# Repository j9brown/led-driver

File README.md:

# LED Driver

Drives 4 RGB/W LEDs with PWM for a total of up to 3 A controlled over an I2C bus.

## Design

This design is based around a [PCA9685](https://www.nxp.com/docs/en/data-sheet/PCA9685.pdf) I2C PWM chip with 16 channels.  Each channel drives an N-channel MOSFET low-side switch.  Each group of 4 channels and a positive common rail feeds a JST XH 5-pin connector to which an RGB/W LED lamp may be attached.

The I2C bus must be referenced to the same ground as the negative input.

The board is designed for use with a 12 V nominal power supply but should work with anything from about 5 V to 16 V.  It includes a 3 A polyfuse and transient voltage suppression.  In case of reverse polarity connection, the TVS shunts the power input across the polyfuse.

## Notice

The software, documentation, design, and all copyright protected artifacts are released under the terms of the [MIT license](LICENSE).

The hardware is released under the terms of the [CERN-OHL-W license](hardware/LICENSE).

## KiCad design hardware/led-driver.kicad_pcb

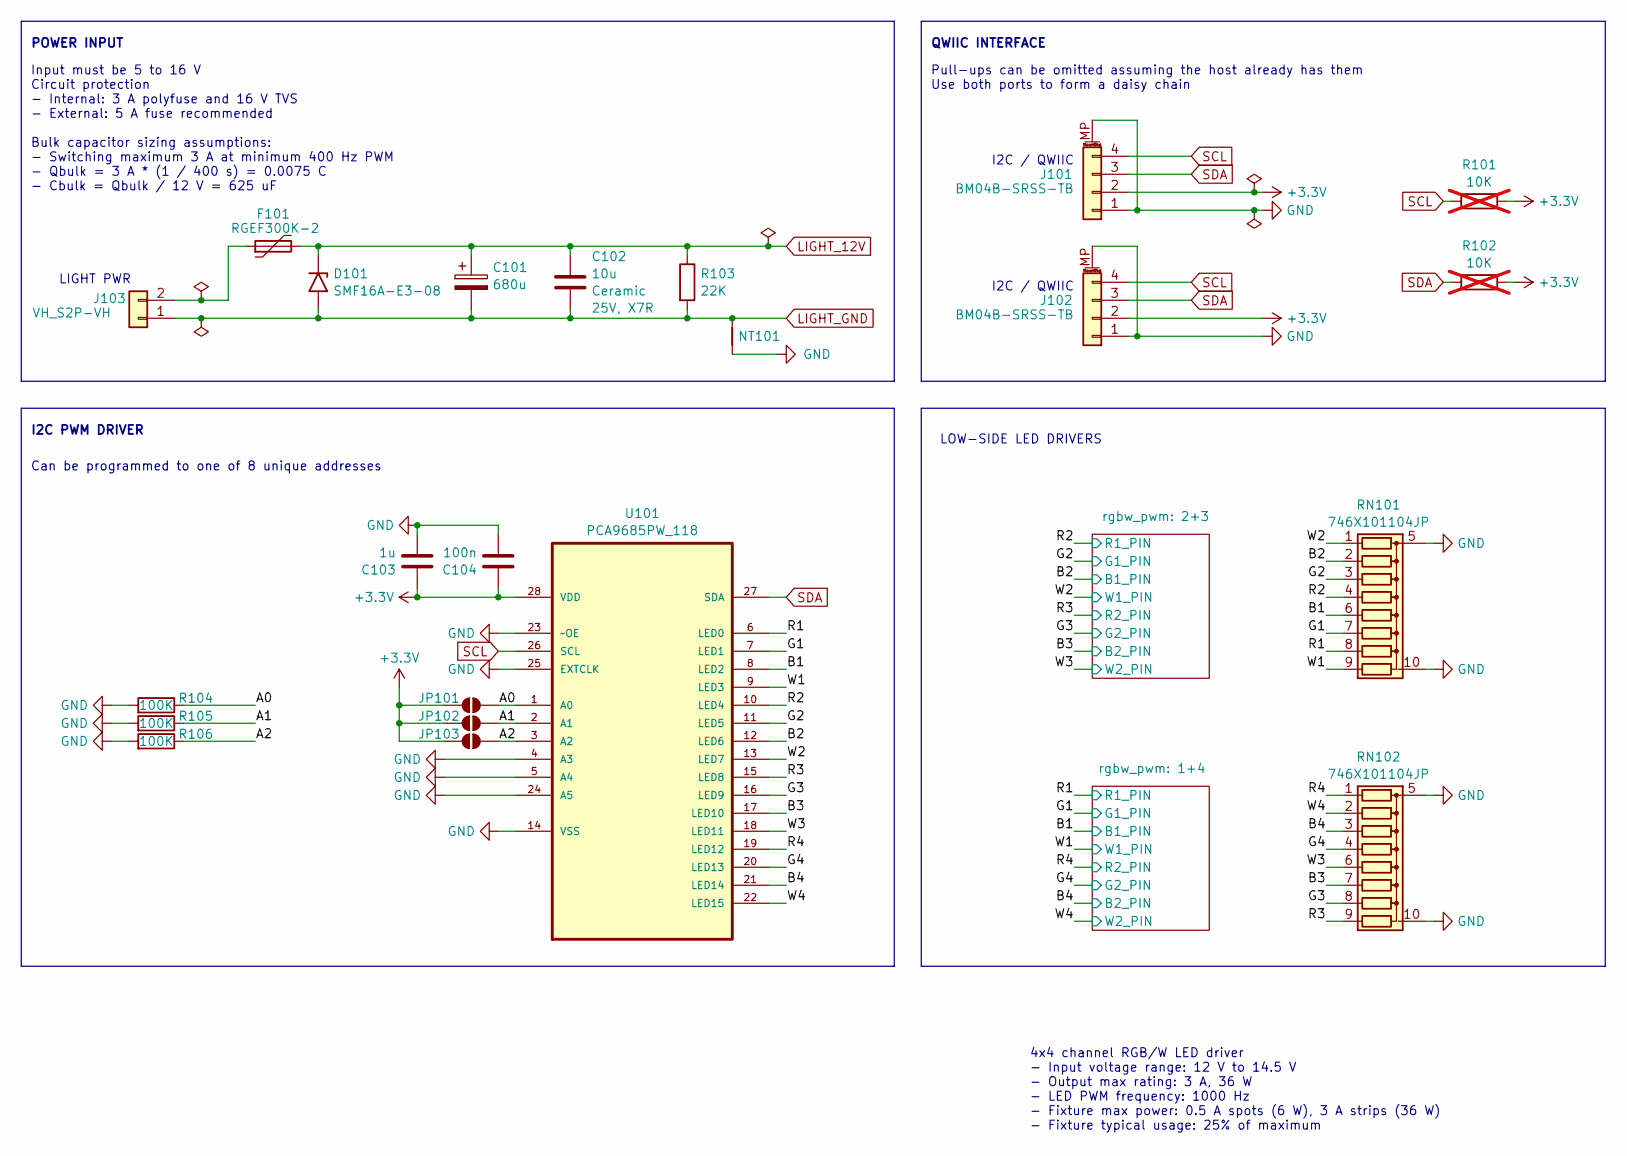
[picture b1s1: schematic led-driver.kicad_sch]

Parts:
C101: 680u; CP_Radial_D10.0mm_P5.00mm; Part EKZH160ELL681MJC5S
C102: 10u; C_1206_3216Metric_Pad1.33x1.80mm_HandSolder; Rating 25V, X7R
C103: 1u; C_0603_1608Metric_Pad1.08x0.95mm_HandSolder
C104: 100n; C_0603_1608Metric_Pad1.08x0.95mm_HandSolder
D101: SMF16A-E3-08; D_SMF
F101: RGEF300K-2; FUSRR505W81L660T250H1360
J101, J102: BM04B-SRSS-TB; JST_SH_BM04B-SRSS-TB_1x04-1MP_P1.00mm_Vertical
J103: VH_S2P-VH; JST_VH_S2P-VH_1x02_P3.96mm_Horizontal
JP101, JP102, JP103: SolderJumper_2_Open; SolderJumper-2_P1.3mm_Open_TrianglePad1.0x1.5mm
NT101: NetTie_2; NetTie-2_SMD_Pad1.6mm
R101, R102: 10K; R_0603_1608Metric_Pad0.98x0.95mm_HandSolder; not fitted
R103: 22K; R_1206_3216Metric_Pad1.30x1.75mm_HandSolder
R104, R105, R106: 100K; R_0603_1608Metric_Pad0.98x0.95mm_HandSolder
RN101, RN102: 746X101104JP; RESCAXS64P320X160X70-10N
U101: PCA9685PW_118; SOP65P640X110-28N; MPN PCA9685PW,118

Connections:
+3.3V: C103.1, C104.1, J101.2, J102.2, JP101.1 (A), JP102.1 (A), JP103.1 (A), R101.1, R102.1, U101.28 (VDD)
/A0: JP101.2 (B), R104.1, U101.1 (A0)
/A1: JP102.2 (B), R105.1, U101.2 (A1)
/A2: JP103.2 (B), R106.1, U101.3 (A2)
/B1: RN101.6 (R5), U101.8 (LED2); also elsewhere on the board
/B2: RN101.2 (R2), U101.12 (LED6); also elsewhere on the board
/B3: RN102.7 (R6), U101.17 (LED10); also elsewhere on the board
/B4: RN102.3 (R3), U101.21 (LED14); also elsewhere on the board
/G1: RN101.7 (R6), U101.7 (LED1); also elsewhere on the board
/G2: RN101.3 (R3), U101.11 (LED5); also elsewhere on the board
/G3: RN102.8 (R7), U101.16 (LED9); also elsewhere on the board
/G4: RN102.4 (R4), U101.20 (LED13); also elsewhere on the board
/R1: RN101.8 (R7), U101.6 (LED0); also elsewhere on the board
/R2: RN101.4 (R4), U101.10 (LED4); also elsewhere on the board
/R3: RN102.9 (R8), U101.15 (LED8); also elsewhere on the board
/R4: RN102.1 (R1), U101.19 (LED12); also elsewhere on the board
/W1: RN101.9 (R8), U101.9 (LED3); also elsewhere on the board
/W2: RN101.1 (R1), U101.13 (LED7); also elsewhere on the board
/W3: RN102.6 (R5), U101.18 (LED11); also elsewhere on the board
/W4: RN102.2 (R2), U101.22 (LED15); also elsewhere on the board
GND: C103.2, C104.2, J101.1, J101.MP (MountPin), J102.1, J102.MP (MountPin), NT101.1, R104.2, R105.2, R106.2, RN101.5 (common), RN101.10 (common), RN102.5 (common), RN102.10 (common), U101.4 (A3), U101.5 (A4), U101.14 (VSS), U101.23 (~OE), U101.24 (A5), U101.25 (EXTCLK)
LIGHT_12V: C101.1, C102.1, D101.1 (A1), F101.2, R103.1; also elsewhere on the board
LIGHT_GND: C101.2, C102.2, D101.2 (A2), J103.1, NT101.2, R103.2; also elsewhere on the board
unnamed: F101.1, J103.2
SCL: J101.4, J102.4, R101.2, U101.26 (SCL)
SDA: J101.3, J102.3, R102.2, U101.27 (SDA)

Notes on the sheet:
4x4 channel RGB/W LED driver - Input voltage range: 12 V to 14.5 V - Output max rating: 3 A, 36 W - LED PWM frequency: 1000 Hz - Fixture max power: 0.5 A spots (6 W), 3 A strips (36 W) - Fixture typical usage: 25% of maximum
QWIIC INTERFACE
I2C PWM DRIVER
POWER INPUT
LOW-SIDE LED DRIVERS
I2C / QWIIC
Pull-ups can be omitted assuming the host already has them Use both ports to form a daisy chain
Input must be 5 to 16 V Circuit protection - Internal: 3 A polyfuse and 16 V TVS - External: 5 A fuse recommended Bulk capacitor sizing assumptions: - Switching maximum 3 A at minimum 400 Hz PWM - Qbulk = 3 A * (1 / 400 s) = 0.0075 C - Cbulk = Qbulk / 12 V = 625 uF
LIGHT PWR
Can be programmed to one of 8 unique addresses

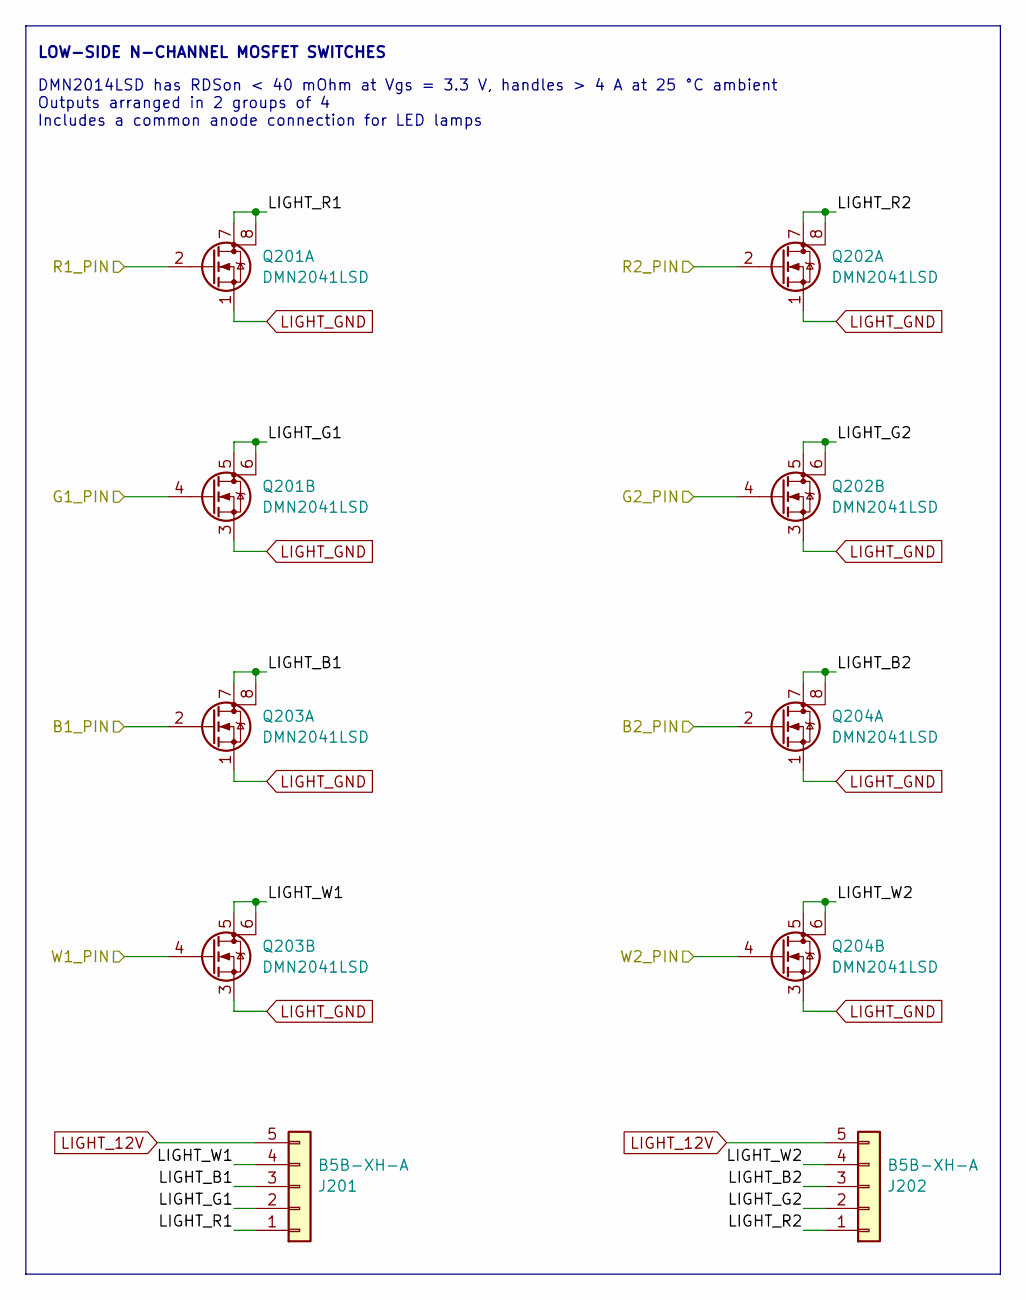
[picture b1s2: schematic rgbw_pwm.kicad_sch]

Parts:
J201, J202: B5B-XH-A; JST_XH_B5B-XH-A_1x05_P2.50mm_Vertical
Q201, Q202, Q203, Q204: DMN2041LSD; SOIC127P600X175-8N

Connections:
/B2: Q203.2 (G); also elsewhere on the board
/B3: Q204.2 (G); also elsewhere on the board
/G2: Q201.4 (G); also elsewhere on the board
/G3: Q202.4 (G); also elsewhere on the board
/R2: Q201.2 (G); also elsewhere on the board
/R3: Q202.2 (G); also elsewhere on the board
/W2: Q203.4 (G); also elsewhere on the board
/W3: Q204.4 (G); also elsewhere on the board
/rgbw_pwm: 2+3/LIGHT_B1: J201.3, Q203.7 (D), Q203.8 (D)
/rgbw_pwm: 2+3/LIGHT_B2: J202.3, Q204.7 (D), Q204.8 (D)
/rgbw_pwm: 2+3/LIGHT_G1: J201.2, Q201.5 (D), Q201.6 (D)
/rgbw_pwm: 2+3/LIGHT_G2: J202.2, Q202.5 (D), Q202.6 (D)
/rgbw_pwm: 2+3/LIGHT_R1: J201.1, Q201.7 (D), Q201.8 (D)
/rgbw_pwm: 2+3/LIGHT_R2: J202.1, Q202.7 (D), Q202.8 (D)
/rgbw_pwm: 2+3/LIGHT_W1: J201.4, Q203.5 (D), Q203.6 (D)
/rgbw_pwm: 2+3/LIGHT_W2: J202.4, Q204.5 (D), Q204.6 (D)
LIGHT_12V: J201.5, J202.5; also elsewhere on the board
LIGHT_GND: Q201.1 (S), Q201.3 (S), Q202.1 (S), Q202.3 (S), Q203.1 (S), Q203.3 (S), Q204.1 (S), Q204.3 (S); also elsewhere on the board

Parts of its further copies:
J301, J302: B5B-XH-A; JST_XH_B5B-XH-A_1x05_P2.50mm_Vertical
Q301, Q302, Q303, Q304: DMN2041LSD; SOIC127P600X175-8N

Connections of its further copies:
/B1: Q303.2 (G); also elsewhere on the board
/B4: Q304.2 (G); also elsewhere on the board
/G1: Q301.4 (G); also elsewhere on the board
/G4: Q302.4 (G); also elsewhere on the board
/R1: Q301.2 (G); also elsewhere on the board
/R4: Q302.2 (G); also elsewhere on the board
/W1: Q303.4 (G); also elsewhere on the board
/W4: Q304.4 (G); also elsewhere on the board
/rgbw_pwm: 1+4/LIGHT_B1: J301.3, Q303.7 (D), Q303.8 (D)
/rgbw_pwm: 1+4/LIGHT_B2: J302.3, Q304.7 (D), Q304.8 (D)
/rgbw_pwm: 1+4/LIGHT_G1: J301.2, Q301.5 (D), Q301.6 (D)
/rgbw_pwm: 1+4/LIGHT_G2: J302.2, Q302.5 (D), Q302.6 (D)
/rgbw_pwm: 1+4/LIGHT_R1: J301.1, Q301.7 (D), Q301.8 (D)
/rgbw_pwm: 1+4/LIGHT_R2: J302.1, Q302.7 (D), Q302.8 (D)
/rgbw_pwm: 1+4/LIGHT_W1: J301.4, Q303.5 (D), Q303.6 (D)
/rgbw_pwm: 1+4/LIGHT_W2: J302.4, Q304.5 (D), Q304.6 (D)
LIGHT_12V: J301.5, J302.5; also elsewhere on the board
LIGHT_GND: Q301.1 (S), Q301.3 (S), Q302.1 (S), Q302.3 (S), Q303.1 (S), Q303.3 (S), Q304.1 (S), Q304.3 (S); also elsewhere on the board

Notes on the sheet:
DMN2014LSD has RDSon < 40 mOhm at Vgs = 3.3 V, handles > 4 A at 25 °C ambient Outputs arranged in 2 groups of 4 Includes a common anode connection for LED lamps
LOW-SIDE N-CHANNEL MOSFET SWITCHES

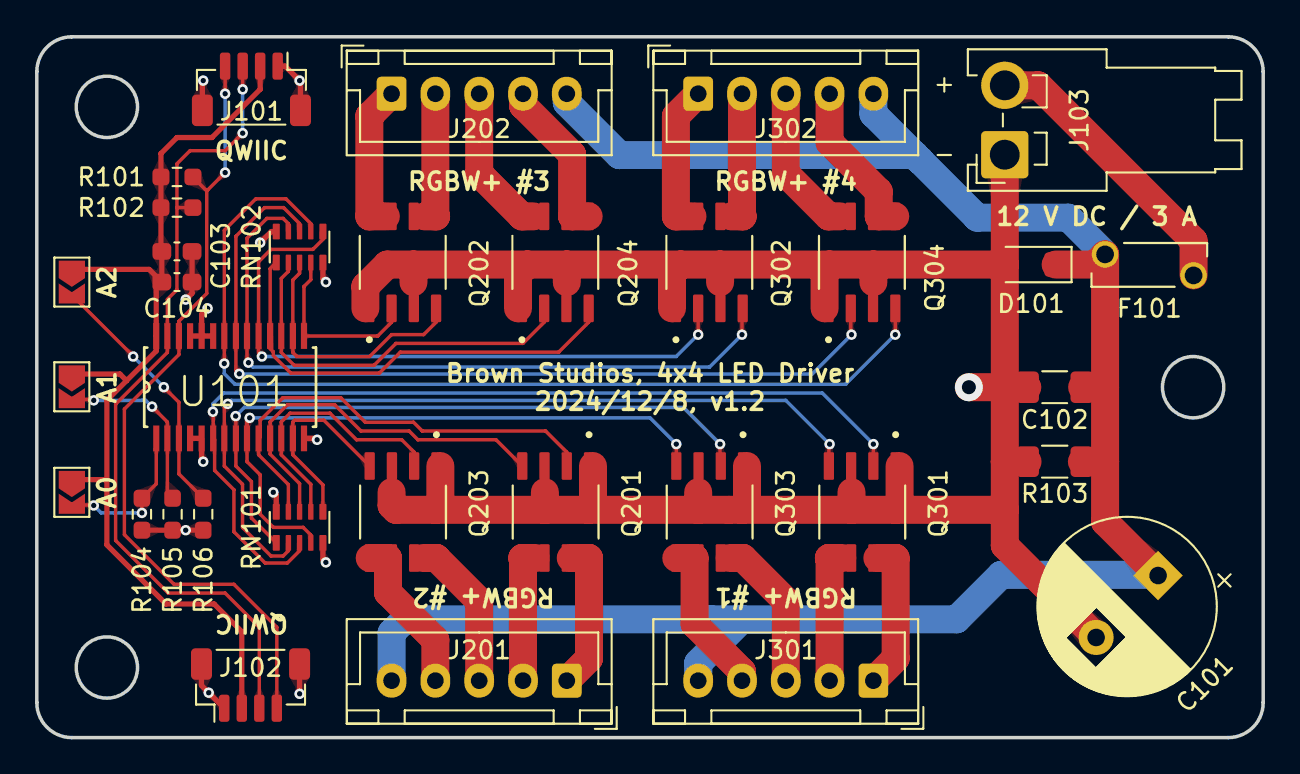
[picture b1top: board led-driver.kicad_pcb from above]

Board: 2 copper layers, 70.0 x 40.0 mm, 34 parts (0 on the bottom side), 42 nets.

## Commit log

2025-05-03 Initial import of the project.
2025-05-03 Tidy up the schematic.
2025-05-03 Add ESPHome configuration package.
2025-05-03 Add PCB rendering
